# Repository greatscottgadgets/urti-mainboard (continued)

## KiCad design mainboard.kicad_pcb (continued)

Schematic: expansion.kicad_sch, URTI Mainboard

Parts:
C52: 1uF; C_0402_1005Metric; Part Number CL05A105MQ5NNNC
J4: PMOD_A; PinSocket_2x06_P2.54mm_PMOD; Part Number DW254W-22-12-85
J5: PMOD_B; PinSocket_2x06_P2.54mm_PMOD; Part Number DW254W-22-12-85
J6: MEZZANINE; Amphenol_10132798-03; Part Number 10132798-031100LF
RN4, RN5, RN6, RN7: 33; R_Array_Convex_4x0402; Part Number YC124-JR-0733RL

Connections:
+3V3: C52.1, J4.6, J4.12, J5.6, J5.12, J6.15, J6.16; also elsewhere on the board
/Expansion Interfaces/A0: J4.1, RN4.8 (R1.2)
/Expansion Interfaces/A1: J4.2, RN4.7 (R2.2)
/Expansion Interfaces/A2: J4.3, RN5.6 (R3.2)
/Expansion Interfaces/A3: J4.4, RN5.8 (R1.2)
/Expansion Interfaces/A4: J4.7, RN4.5 (R4.2)
/Expansion Interfaces/A5: J4.8, RN4.6 (R3.2)
/Expansion Interfaces/A6: J4.9, RN5.5 (R4.2)
/Expansion Interfaces/A7: J4.10, RN5.7 (R2.2)
/Expansion Interfaces/B0: J5.1, RN7.5 (R4.2)
/Expansion Interfaces/B1: J5.2, RN7.7 (R2.2)
/Expansion Interfaces/B2: J5.3, RN6.5 (R4.2)
/Expansion Interfaces/B3: J5.4, RN6.7 (R2.2)
/Expansion Interfaces/B4: J5.7, RN7.6 (R3.2)
/Expansion Interfaces/B5: J5.8, RN7.8 (R1.2)
/Expansion Interfaces/B6: J5.9, RN6.6 (R3.2)
/Expansion Interfaces/B7: J5.10, RN6.8 (R1.2)
/Expansion Interfaces/MEZZANINE3: J6.3; also elsewhere on the board
/Expansion Interfaces/MEZZANINE4: J6.4; also elsewhere on the board
/Expansion Interfaces/MEZZANINE5: J6.5; also elsewhere on the board
/Expansion Interfaces/MEZZANINE6: J6.6; also elsewhere on the board
/Expansion Interfaces/MEZZANINE7: J6.7; also elsewhere on the board
/Expansion Interfaces/MEZZANINE8: J6.8; also elsewhere on the board
/Expansion Interfaces/MEZZANINE9: J6.9; also elsewhere on the board
/Expansion Interfaces/MEZZANINE10: J6.10; also elsewhere on the board
/Expansion Interfaces/MEZZANINE11: J6.11; also elsewhere on the board
/Expansion Interfaces/MEZZANINE12: J6.12; also elsewhere on the board
/Expansion Interfaces/MEZZANINE13: J6.13; also elsewhere on the board
/Expansion Interfaces/MEZZANINE18: J6.18; also elsewhere on the board
/Expansion Interfaces/MEZZANINE19: J6.19; also elsewhere on the board
/Expansion Interfaces/MEZZANINE20: J6.20; also elsewhere on the board
/Expansion Interfaces/MEZZANINE21: J6.21; also elsewhere on the board
/Expansion Interfaces/MEZZANINE22: J6.22; also elsewhere on the board
/Expansion Interfaces/MEZZANINE23: J6.23; also elsewhere on the board
/Expansion Interfaces/MEZZANINE24: J6.24; also elsewhere on the board
/Expansion Interfaces/MEZZANINE25: J6.25; also elsewhere on the board
/Expansion Interfaces/MEZZANINE26: J6.26; also elsewhere on the board
/Expansion Interfaces/MEZZANINE27: J6.27; also elsewhere on the board
/Expansion Interfaces/MEZZANINE28: J6.28; also elsewhere on the board
/Expansion Interfaces/PMOD_A0: RN4.1 (R1.1); also elsewhere on the board
/Expansion Interfaces/PMOD_A1: RN4.2 (R2.1); also elsewhere on the board
/Expansion Interfaces/PMOD_A2: RN5.3 (R3.1); also elsewhere on the board
/Expansion Interfaces/PMOD_A3: RN5.1 (R1.1); also elsewhere on the board
/Expansion Interfaces/PMOD_A4: RN4.4 (R4.1); also elsewhere on the board
/Expansion Interfaces/PMOD_A5: RN4.3 (R3.1); also elsewhere on the board
/Expansion Interfaces/PMOD_A6: RN5.4 (R4.1); also elsewhere on the board
/Expansion Interfaces/PMOD_A7: RN5.2 (R2.1); also elsewhere on the board
/Expansion Interfaces/PMOD_B0: RN7.4 (R4.1); also elsewhere on the board
/Expansion Interfaces/PMOD_B1: RN7.2 (R2.1); also elsewhere on the board
/Expansion Interfaces/PMOD_B2: RN6.4 (R4.1); also elsewhere on the board
/Expansion Interfaces/PMOD_B3: RN6.2 (R2.1); also elsewhere on the board
/Expansion Interfaces/PMOD_B4: RN7.3 (R3.1); also elsewhere on the board
/Expansion Interfaces/PMOD_B5: RN7.1 (R1.1); also elsewhere on the board
/Expansion Interfaces/PMOD_B6: RN6.3 (R3.1); also elsewhere on the board
/Expansion Interfaces/PMOD_B7: RN6.1 (R1.1); also elsewhere on the board
GND: C52.2, J4.5, J4.11, J5.5, J5.11, J6.2, J6.14, J6.17, J6.29, J6.MP (MountPin); also elsewhere on the board

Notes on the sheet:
Pmod
Mezzanine

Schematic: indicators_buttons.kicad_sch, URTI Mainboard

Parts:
C53, C54: 1uF; C_0402_1005Metric; Part Number CL05A105MQ5NNNC
D1: BLUE; LED_0603_1608Metric; Part Number ORH-B36G
D2: GREEN; LED_0603_1608Metric; Part Number ORH-G36G
D3: YELLOW; LED_0603_1608Metric; Part Number E6C0603UYAC1UDA
D4: ORANGE; LED_0603_1608Metric; Part Number E6C0603SEAC1UDA
D5: RED; LED_0603_1608Metric; Part Number OSR50603C1E
D6: PURPLE; LED_0603_1608Metric; Part Number OSVX0603C1E
D10, D14: ICE BLUE; LED_0603_1608Metric; Part Number MHT192WDT-ICE
D11, D13: PINK; LED_0603_1608Metric; Part Number OSK40603C1E
D12: WHITE; LED_0603_1608Metric; Part Number ORH-W46G
R22, R27: 10k; R_0402_1005Metric; Part Number RC0402JR-0710KL
R23: 33k; R_0402_1005Metric; Part Number ERJ-2GEJ333X
R24, R25, R26: 1k; R_0402_1005Metric; Part Number RC0402JR-071KL
R28, R29, R32, R34, R35: 2.2k; R_0402_1005Metric; Part Number RC0402JR-072K2L
R30, R36: 5.1k; R_0402_1005Metric; Part Number RC0402JR-075K1L
R31: 8.06k±1%; R_0402_1005Metric; Part Number ERJ-2RKF8061X
R33: 18.7k±1%; R_0402_1005Metric; Part Number ERJ-2RKF1872X
SW1: BTN_PROGRAM; SW_Tactile_SPST_Angled_TC-1109DE-B-F; Part Number TC-1109DE-B-F
SW2: BTN_RESET; SW_Tactile_SPST_Angled_TC-1109DE-B-F; Part Number TC-1109DE-B-F
SW3: BTN_USER; SW_Tactile_SPST_Angled_TC-1109DE-B-F; Part Number TC-1109DE-B-F
TP14, TP15, TP16, TP17, TP18, TP19, TP20, TP21, TP22, TP23, TP24, TP25: TestPoint; TestPoint_Pad_D1.0mm

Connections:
+3V3: D1.2 (A), D2.2 (A), D3.2 (A), D4.2 (A), D5.2 (A), D6.2 (A), R22.1, R30.1, R31.1, R32.1, R34.1, R35.1, R36.1; also elsewhere on the board
/Debugger/LED10: D10.1 (K); also elsewhere on the board
/Debugger/LED11: D11.1 (K); also elsewhere on the board
/Debugger/LED12: D12.1 (K); also elsewhere on the board
/Debugger/LED13: D13.1 (K); also elsewhere on the board
/Debugger/LED14: D14.1 (K); also elsewhere on the board
/Debugger/~BTN_PROGRAM: C54.1, R33.1; also elsewhere on the board
/Debugger/~BTN_RESET: SW2.1; also elsewhere on the board
/FPGA Banks 0 and 1/LED0: R29.2; also elsewhere on the board
/FPGA Banks 0 and 1/LED1: R28.2; also elsewhere on the board
/FPGA Banks 0 and 1/LED2: R27.2; also elsewhere on the board
/FPGA Banks 0 and 1/LED3: R26.2; also elsewhere on the board
/FPGA Banks 0 and 1/LED4: R25.2; also elsewhere on the board
/FPGA Banks 0 and 1/LED5: R24.2; also elsewhere on the board
/FPGA Banks 2 and 3/~BTN_USER: C53.1, R23.1; also elsewhere on the board
GND: C53.2, C54.2, SW1.2, SW1.3 (SHIELD), SW2.2, SW2.3 (SHIELD), SW3.2, SW3.3 (SHIELD); also elsewhere on the board
unnamed: D1.1 (K), R28.1, TP18.1
unnamed: D2.1 (K), R27.1, TP17.1
unnamed: D3.1 (K), R26.1, TP16.1
unnamed: D4.1 (K), R25.1, TP15.1
unnamed: D5.1 (K), R24.1, TP14.1
unnamed: D6.1 (K), R29.1, TP19.1
unnamed: D10.2 (A), R30.2, TP21.1
unnamed: D11.2 (A), R32.2, TP22.1
unnamed: D12.2 (A), R34.2, TP23.1
unnamed: D13.2 (A), R35.2, TP24.1
unnamed: D14.2 (A), R36.2, TP25.1
unnamed: R22.2, R23.2, SW3.1
unnamed: R31.2, R33.2, SW1.1, TP20.1

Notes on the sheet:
FPGA Button
Debugger Buttons
FPGA LEDs 5-0
Debugger LEDs A-E

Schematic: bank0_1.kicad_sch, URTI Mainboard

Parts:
U1: ECP5-BGA256; lattice_cabga256; Part Number LFE5U-12F-6BG256C

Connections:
+3V3: U1.D10 (PT47A), U1.E6 (PT20A), U1.E7 (PT24A), U1.E10 (PT47B), U1.E11 (PT51B), U1.F6 (VCCIO0_1), U1.F7 (VCCIO0_2), U1.F10 (VCCIO1_1), U1.F11 (VCCIO1_2); also elsewhere on the board
/Clock and Miscellaneous/CLOCK_60MHZ: U1.A8 (PT29B); also elsewhere on the board
/Expansion Interfaces/MEZZANINE3: U1.B8 (PT35B); also elsewhere on the board
/Expansion Interfaces/MEZZANINE4: U1.A9 (PT42A); also elsewhere on the board
/Expansion Interfaces/MEZZANINE5: U1.B10 (PT44A); also elsewhere on the board
/Expansion Interfaces/MEZZANINE6: U1.A10 (PT42B); also elsewhere on the board
/Expansion Interfaces/MEZZANINE7: U1.B11 (PT49A); also elsewhere on the board
/Expansion Interfaces/MEZZANINE22: U1.A14 (PT65B); also elsewhere on the board
/Expansion Interfaces/MEZZANINE23: U1.B13 (PT60A); also elsewhere on the board
/Expansion Interfaces/MEZZANINE24: U1.A13 (PT65A); also elsewhere on the board
/Expansion Interfaces/MEZZANINE25: U1.D13 (PT62A); also elsewhere on the board
/Expansion Interfaces/MEZZANINE26: U1.A12 (PT53B); also elsewhere on the board
/Expansion Interfaces/MEZZANINE27: U1.B12 (PT56A); also elsewhere on the board
/Expansion Interfaces/MEZZANINE28: U1.A11 (PT53A); also elsewhere on the board
/Expansion Interfaces/PMOD_A0: U1.C9 (PT38B); also elsewhere on the board
/Expansion Interfaces/PMOD_A1: U1.B9 (PT38A); also elsewhere on the board
/Expansion Interfaces/PMOD_A2: U1.D11 (PT51A); also elsewhere on the board
/Expansion Interfaces/PMOD_A3: U1.C12 (PT56B); also elsewhere on the board
/Expansion Interfaces/PMOD_A4: U1.C8 (PT35A); also elsewhere on the board
/Expansion Interfaces/PMOD_A5: U1.D8 (PT33B); also elsewhere on the board
/Expansion Interfaces/PMOD_A6: U1.D9 (PT40A); also elsewhere on the board
/Expansion Interfaces/PMOD_A7: U1.C10 (PT44B); also elsewhere on the board
/Expansion Interfaces/PMOD_B0: U1.B4 (PT11B); also elsewhere on the board
/Expansion Interfaces/PMOD_B1: U1.B5 (PT15B); also elsewhere on the board
/Expansion Interfaces/PMOD_B2: U1.B6 (PT22B); also elsewhere on the board
/Expansion Interfaces/PMOD_B3: U1.B7 (PT27B); also elsewhere on the board
/Expansion Interfaces/PMOD_B4: U1.C5 (PT15A); also elsewhere on the board
/Expansion Interfaces/PMOD_B5: U1.A5 (PT18A); also elsewhere on the board
/Expansion Interfaces/PMOD_B6: U1.A6 (PT18B); also elsewhere on the board
/Expansion Interfaces/PMOD_B7: U1.A7 (PT29A); also elsewhere on the board
/FPGA Banks 0 and 1/LED0: U1.E13 (PT62B); also elsewhere on the board
/FPGA Banks 0 and 1/LED1: U1.C13 (PT60B); also elsewhere on the board
/FPGA Banks 0 and 1/LED2: U1.B14 (PT67A); also elsewhere on the board
/FPGA Banks 0 and 1/LED3: U1.A15 (PT67B); also elsewhere on the board
/FPGA Banks 0 and 1/LED4: U1.D12 (PT58A); also elsewhere on the board
/FPGA Banks 0 and 1/LED5: U1.C11 (PT49B); also elsewhere on the board
GND: U1.E5 (PT13A), U1.E8 (PT33A), U1.E9 (PT40B), U1.E12 (PT58B); also elsewhere on the board

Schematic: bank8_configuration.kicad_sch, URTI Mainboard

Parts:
C55: 0.1uF; C_0402_1005Metric; Part Number CL05A104KA5NNNC
R37, R40, R43: 5.1k; R_0402_1005Metric; Part Number RC0402JR-075K1L
R38: 10k; R_0402_1005Metric; Part Number RC0402JR-0710KL
R39, R41: 330; R_0402_1005Metric; Part Number RC0402FR-13330RL
R42, R44: 2.2k; R_0402_1005Metric; Part Number RC0402JR-072K2L
TP26, TP27, TP28, TP29, TP30, TP31, TP32, TP33: TestPoint; TestPoint_Pad_D1.0mm
U1: ECP5-BGA256; lattice_cabga256; Part Number LFE5U-12F-6BG256C
U10: W25Q32JVSS; SOIC-8_5.23x5.23mm_P1.27mm; Part Number W25Q32JVSSIQ

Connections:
+3V3: C55.1, R37.1, R38.1, R40.2, R43.1, U1.L6 (VCCIO8), U1.R6 (D6/PB4B), U10.8 (VCC); also elsewhere on the board
/Debugger/FPGA_ADV: U1.T6 (D7/PB4A); also elsewhere on the board
/Debugger/FPGA_CONFIG.DONE: TP32.1, U1.P9 (DONE); also elsewhere on the board
/Debugger/FPGA_CONFIG.~INIT: R42.1, U1.T9 (INITN); also elsewhere on the board
/Debugger/FPGA_CONFIG.~PROGRAM: R43.2, R44.1, TP33.1, U1.R9 (PROGRAMN); also elsewhere on the board
/Debugger/FPGA_JTAG.TCK: TP28.1, U1.T10 (TCK); also elsewhere on the board
/Debugger/FPGA_JTAG.TDI: TP31.1, U1.R11 (TDI); also elsewhere on the board
/Debugger/FPGA_JTAG.TDO: TP30.1, U1.M10 (TDO); also elsewhere on the board
/Debugger/FPGA_JTAG.TMS: TP29.1, U1.T11 (TMS); also elsewhere on the board
/FPGA Bank 8 and Configuration Flash/D0: U1.T8 (D0/PICO/PB11B), U10.5 (DI(IO0))
/FPGA Bank 8 and Configuration Flash/D1: U1.T7 (D1/POCI/PB11A), U10.2 (DO(IO1))
/FPGA Bank 8 and Configuration Flash/D2: U1.M7 (D2/PB9B), U10.3 (IO2)
/FPGA Bank 8 and Configuration Flash/D3: U1.N7 (D3/PB9A), U10.7 (IO3)
/FPGA Bank 8 and Configuration Flash/FPGA_CFG0: R39.1, U1.N10 (CFG_0)
/FPGA Bank 8 and Configuration Flash/FPGA_CFG1: R40.1, U1.P10 (CFG_1)
/FPGA Bank 8 and Configuration Flash/FPGA_CFG2: R41.1, U1.R10 (CFG_2)
/FPGA Bank 8 and Configuration Flash/FPGA_FLASH_CLK: R37.2, TP26.1, U1.N9 (MCLK/SCLK/CCLK), U10.6 (CLK)
/FPGA Bank 8 and Configuration Flash/~CS_DI: R38.2, TP27.1, U1.N8 (HOLDN/DI/PB15A), U10.1 (~CS)
/FPGA Bank 8 and Configuration Flash/~FPGA_SELF_PROGRAM: R44.2; also elsewhere on the board
GND: C55.2, R39.2, R41.2, R42.2, U10.4 (GND); also elsewhere on the board

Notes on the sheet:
By default, select MSPI mode, so the ECP5 will self-configure from flash.
FPGA_ADV is a unidirectional UART for the FPGA to advertise status or requests to the microcontroller.
Remove R44 to prevent FPGA from triggering its own programming

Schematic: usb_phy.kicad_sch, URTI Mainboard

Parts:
C48, C49: 1uF; C_0402_1005Metric; Part Number CL05A105MQ5NNNC
C50, C51: 0.1uF; C_0402_1005Metric; Part Number CL05A104KA5NNNC
FL1: Filter_EMI_CommonMode; L_CommonModeChoke_Murata_DLM0NS; Part Number DLM0NSN900HY2D
R19: 20k; R_0402_1005Metric; Part Number RC0402JR-0720KL
R20: 8.06k±1%; R_0402_1005Metric; Part Number ERJ-2RKF8061X
R21: 10k; R_0402_1005Metric; Part Number RC0402JR-0710KL
RN1, RN2, RN3: 330; R_Array_Convex_4x0402; Part Number YC124-JR-07330RL
TP12, TP13: TestPoint; TestPoint_Pad_D1.0mm
U9: USB3343-CP; VQFN-24-1EP_4x4mm_P0.5mm_EP2.45x2.45mm; Part Number USB3343-CP

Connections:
+3V3: C48.1, C50.1, C51.1, TP13.1, U9.2 (CLKOUT), U9.9 (VDDIO), U9.15 (VDD33), U9.16 (VBAT), U9.18 (ID); also elsewhere on the board
+5V: R19.1; also elsewhere on the board
/CONTROL Port/CONTROL PHY/CLK: RN3.8 (R1.2), U9.21 (REFCLK/XI)
/CONTROL Port/CONTROL PHY/D+: FL1.1, U9.14 (D+)
/CONTROL Port/CONTROL PHY/D-: FL1.3, U9.13 (D-)
/CONTROL Port/CONTROL PHY/DATA0: RN1.8 (R1.2), U9.4 (DATA0)
/CONTROL Port/CONTROL PHY/DATA1: RN1.7 (R2.2), U9.5 (DATA1)
/CONTROL Port/CONTROL PHY/DATA2: RN1.6 (R3.2), U9.6 (DATA2)
/CONTROL Port/CONTROL PHY/DATA3: RN1.5 (R4.2), U9.7 (DATA3)
/CONTROL Port/CONTROL PHY/DATA4: RN2.8 (R1.2), U9.8 (DATA4)
/CONTROL Port/CONTROL PHY/DATA5: RN2.7 (R2.2), U9.10 (DATA5)
/CONTROL Port/CONTROL PHY/DATA6: RN2.6 (R3.2), U9.11 (DATA6)
/CONTROL Port/CONTROL PHY/DATA7: RN2.5 (R4.2), U9.12 (DATA7)
/CONTROL Port/CONTROL PHY/DIR: RN3.6 (R3.2), U9.1 (DIR)
/CONTROL Port/CONTROL PHY/NXT: RN3.5 (R4.2), U9.3 (NXT)
/CONTROL Port/CONTROL PHY/PHY_D+: FL1.2; also elsewhere on the board
/CONTROL Port/CONTROL PHY/PHY_D-: FL1.4; also elsewhere on the board
/CONTROL Port/CONTROL PHY/RBIAS: R20.2, U9.19 (RBIAS)
/CONTROL Port/CONTROL PHY/STP: RN3.7 (R2.2), U9.24 (STP)
/CONTROL Port/CONTROL PHY/VBUS_SENSE: R19.2, U9.17 (VBUS)
/CONTROL Port/CONTROL PHY/VDD18: C49.1, TP12.1, U9.23 (VDD18)
/CONTROL Port/CONTROL_PHY.CLK: RN3.1 (R1.1); also elsewhere on the board
/CONTROL Port/CONTROL_PHY.DATA0: RN1.1 (R1.1); also elsewhere on the board
/CONTROL Port/CONTROL_PHY.DATA1: RN1.2 (R2.1); also elsewhere on the board
/CONTROL Port/CONTROL_PHY.DATA2: RN1.3 (R3.1); also elsewhere on the board
/CONTROL Port/CONTROL_PHY.DATA3: RN1.4 (R4.1); also elsewhere on the board
/CONTROL Port/CONTROL_PHY.DATA4: RN2.1 (R1.1); also elsewhere on the board
/CONTROL Port/CONTROL_PHY.DATA5: RN2.2 (R2.1); also elsewhere on the board
/CONTROL Port/CONTROL_PHY.DATA6: RN2.3 (R3.1); also elsewhere on the board
/CONTROL Port/CONTROL_PHY.DATA7: RN2.4 (R4.1); also elsewhere on the board
/CONTROL Port/CONTROL_PHY.DIR: RN3.3 (R3.1); also elsewhere on the board
/CONTROL Port/CONTROL_PHY.NXT: RN3.4 (R4.1); also elsewhere on the board
/CONTROL Port/CONTROL_PHY.STP: RN3.2 (R2.1); also elsewhere on the board
/CONTROL Port/CONTROL_PHY.~RESET: R21.1, U9.22 (RESET); also elsewhere on the board
GND: C48.2, C49.2, C50.2, C51.2, R20.1, R21.2, U9.25 (GND); also elsewhere on the board

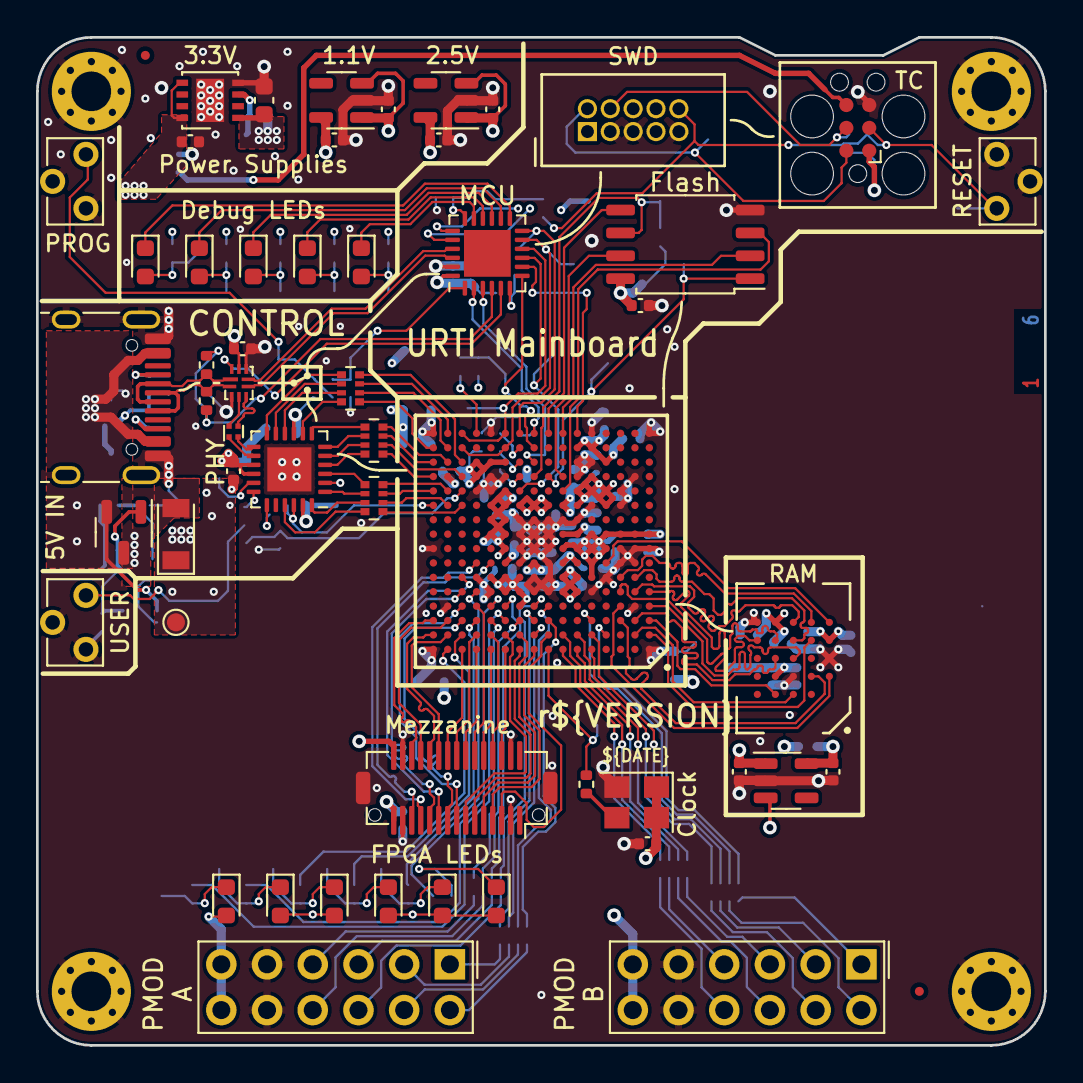
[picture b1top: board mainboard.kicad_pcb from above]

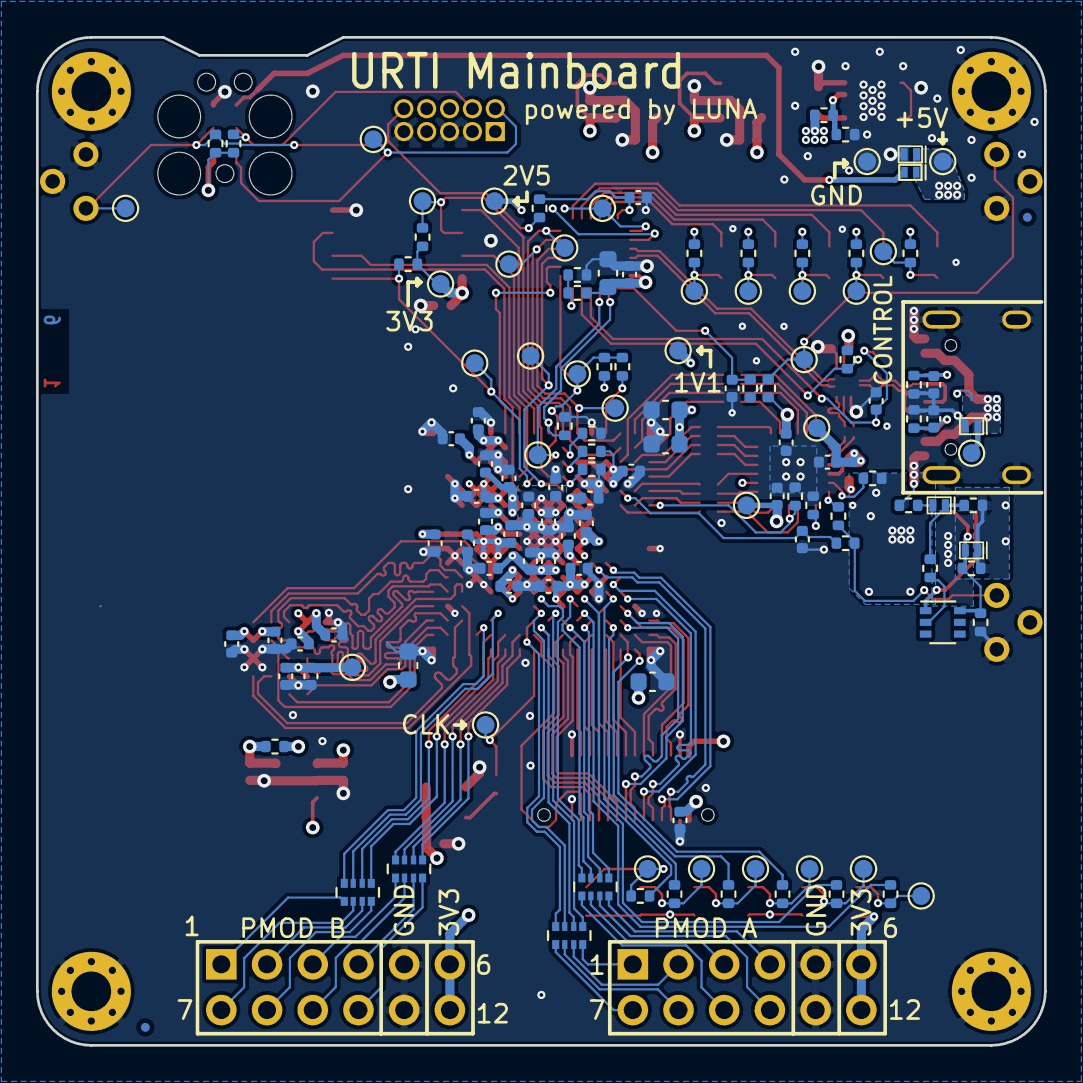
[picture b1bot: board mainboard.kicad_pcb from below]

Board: 6 copper layers, 56.0 x 56.0 mm, 190 parts (131 on the bottom side), 172 nets.

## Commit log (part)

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2023-09-29 First commit, derived from Cynthion r1.3.0
2024-01-17 Add radio transceiver
    Remove Cynthion-specific features
2024-01-19 Update mcu pin assignments to support fast JTAG
2024-02-26 Add missing solder mask apertures
2024-02-26 Replace open drain clock inverters with push-pull
2024-02-27 Tune slow-start capacitors
2024-02-27 Tune clock passives
